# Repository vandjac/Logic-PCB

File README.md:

## Table of Contents
***
1. [General Info](#general-info)
2. [Design Requirements](#design-requirements) 
   - [Boolean Logic](#boolean-logic)
   - [Flip Flops](#flip-flops)
   - [Power](#power)
   - [Silk Screen](#silk-screen)
   - [Dimensions](#dimensions)
3. [Detailed Schematic Info](#detailed-schematic-info)
   - [Input Power](#input-power)
      - [USB-C Connector](#usb-c-connector)
      - [5V to 3.3V Linear Regulator](#linear-regulator)
      - [On/Off Switch](#power-switch)
      - [Battery Considerations](#battery-considerations)
   - [Buttons](#buttons)
   - [LEDs](#leds)
   - [Logic Gates](#logic-gates)
      - [NOT Gate](#not-gate)
      - [AND Gate](#and-gate)
      - [OR Gate](#or-gate)
      - [NAND Gate](#nand-gate)
      - [NOR Gate](#nor-gate)
      - [XOR Gate](#xor-gate)
      - [XNOR Gate](#xnor-gate)
   - [Flip Flops and Latches](#flip-flops-and-latches)
      - [D Flip Flop](#d-flip-flop)
      - [JK Flip Flop](#jk-flip-flop)
      - [T Flip Flop](#t-flip-flop)
      - [SR Latch](#sr-latch)
   - [Adjustable Clock Generator](#adjustable-clock-generator)
   - [State Machine](#state-machine)
   - [Synchronous 3-Bit 0-5 Counter](#synchronous-3-bit-0-5-counter)
   - [Multiplexers and 16-Segment Display](#multiplexers-and-16-segment-display)
4. [KiCAD](#kicad)
   - [Schematic Design](#schematic-design)
   - [PCB Layout](#pcb-layout)
      - [Images](#images)
5. [Possible Improvements](#possible-improvements)
6. [Acknowledgements](#acknowledgements)

## General Info
***
This is a quick-turn promotional PCB made as an intern project for Gentex Corporation. It showcases digital logic concepts in an interactive format, and will be a useful reference for students studying digital electronics.

## Design Requirements
***
#### Boolean Logic
* The design shall include the following Boolean logic gates:
   - AND 
    - OR 
    - XOR 
    - NOR 
    - NAND 
    - NOT 
    - XNOR 
* The design shall electrically demonstrate each logic gate. 
* The design shall include a silk screen that captures all of the logic gate truth tables. 
* The design shall include 2 inputs for each logic gate. 
#### Flip Flops
* The design shall implement a minimum of one (1) flip-flop. 
* The design shall electrically demonstrate all implemented flip-flops. 
* The design shall include a silk screen that captures each implemented flip-flop truth table. 
#### Power
* The design shall operate on 3.0V power. 
* The design shall be powered from either a coin cell battery, or external power supply. 
#### Silk Screen
* The design shall implement the Gentex logo on the silk screen layer. 
* The design shall implement the designer's college on the silk screen layer. 
#### Dimensions
* The design shall be implemented on a 3”x5” PCB. 
## [Detailed Schematic Info](https://github.com/vandjac/Logic-PCB/files/12321933/Logic-PCB-Schematic.pdf)
***
### Input Power
***
According to the project requirements, the board had to operate at 3V. When choosing input power, that left us with a couple options. Either we could use power from a USB input, or we could use a coin cell battery. Each had their advantages, but we decided on using USB power only. Although the coin cell battery allows for the board to be portable, it didn’t have enough capacity or current sourcing capabilities to be worth the addition.

We did a power analysis on our design to determine the max current that would theoretically be drawn. With 17 LEDs pulling 5-10mA, a max of 8 segments of the 16-digit display being on at 10mA, and the linear regulator at 45mA, our max current draw was around 200-300mA.

#### USB-C Connector

This USB-C connector is power only, which means it has fewer pins than a standard USB-C jack. This makes the pads bigger and easier to solder onto. The pins that are included are 2 VBUS, 2 GND, and 2 CC pins. The CC pins are used to regulate the current draw from the power source. In order to activate the power source, we have to add a 5.1k resistor to each CC pin. The USB-C should be able to supply 5V at up to 500mA, which should be enough for all functions on the board.

#### Linear Regulator

The chosen linear regulator can convert 5V to 3.3V with a max output current of 400mA. Another consideration for the regulator is heat dissipation, which could be problematic at max output current. The calculation for determining the temperature of the part is as follows:

Rthja×voltage drop×current draw

With the SOT-223 package, the temperature comes out to (87)(1.7)(0.4)=59.16°C

With the DPAK package, the temperature comes out to (72.5)(1.7)(0.4)=49.3°C

The industry standard is that anything over 60°C is too hot to touch, so the DPAK package is more appropriate for this case. This package is larger than the SOT-223.

The circuit design was copied from the datasheet for the linear regulator. The datasheet provides different configurations depending on the desired output voltage. A .1u bypass capacitor is also added to the output to smooth out voltage spikes.

#### Power Switch

The main consideration for the switch was how much current it could handle, since the entire power for the board was being routed through the switch. For the JS203011JAQN switch being used, the datasheet gives a contact rating of 0.3A@6VDC. Since we’re using 3V power, we should be able to get more than 0.3A through it, if needed.

#### Battery Considerations

In the event that someone would want to add a battery to the board, we have kept the schematics for the battery in the design, but commented out. If a battery were to be added in conjunction with USB power, it would be necessary to ensure that the two power sources don’t fight. To do so, Schottky diodes are placed on the 3V outputs of the battery holder and the linear regulator. These diodes have a low voltage drop (0.3V) and block current from flowing back into the battery or regulator. 

In reality, the Schottky diode on the regulator wouldn’t be doing much. This is because the regulator outputs a constant 3.3V, while the battery will always be at 3V or less. Therefore, current would only try to flow from the regulator to the battery. However, it is good practice to have Schottky diodes placed on both sources.

### Buttons
***

Originally, we were planning on having individual buttons for each logic gate and flip flop. We quickly realized that would be a waste of space. Now, we have two buttons (labeled A and B) that control all the logic gates and flip flops on the board. 

Each button has a pulldown resistor and two capacitors. The pulldown is there to make sure the button line is held low when the button is not pressed. The 1u capacitor helps to debounce the button, and the .1u capacitor is a bypass capacitor to eliminate voltage spikes. 

As for the specific button chosen, we simply found one in a small 6x6mm package that Gentex had in stock.

### LEDs
***
Each LED is set up to run at a max of 10mA. The LEDs have a voltage drop of 2V. 3.3V is taken from the pins on the ICs or from VCC, depending on the circuit. Therefore, we are left with V=IR, where V=1.3, I=13mA, and R=100Ω. That can easily be changed to V=1.3, I=6.5mA, and R=200Ω with a change of resistors.

Because we have the LEDs sinking current from ICs, we had to ensure that each IC was capable of sinking 10mA of current. The ICs we chose have that capability.

### Logic Gates
***
Logic gates are fundamental building blocks of digital circuits and are used to perform logical operations. According to the project requirements, the common 7 logic gates: AND, OR, NOT, XOR, NOR, XNOR, NAND. This was implemented with the use of NPN, PNP, P-channel, N-channel CMOS transistors, LEDs, resistors, and buttons A & B.

#### NOT Gate

The NOT gate, also known as an inverter, is a logical component that takes a single input signal and generates an output signal that is the inverse of the input. Specifically, when the input signal is at a high state (1), the output signal is at a low state (0), and conversely, when the input is low (0), the output is high (1). To achieve this functionality, a circuit was designed in which the power flows through a resistor and an LED connected to the collector of a PNP transistor. Initially, when the board is powered on, the LED is lit, indicating a high (1) output as button A remains untouched, signifying a low (0) input. However, when button A is pressed, causing a high (1) input, power is directed through the base of the PNP transistor, resulting in the LED being turned off, thereby representing a low (0) output state.

Truth Table:

| Input | Output |
|:---------:|:---------:|
| 0 | 1 |
| 1 | 0 |

#### AND Gate

The AND gate is a logic circuit that takes two or more input signals and generates a single output signal. The output signal is set to low (0) whenever any of the input signals are low (0). However, if all the input signals are high (1), the output will be high (1) as well. 

To implement this logic, the AND gate circuit utilizes two NPN transistors connected in series in the collector-emitter configuration with a resistor and an LED connected to the emitter. Initially, when the circuit is powered on, the LED remains off, indicating a low (0) output because neither button A nor B has been pressed, and no power flows through the transistors to activate the LED. Since the transistors are in series, pressing only one button (making it high) while the other remains low (0) continues to prevent power from reaching the LED, keeping the output low (0). However, when both buttons are pressed (making them high), power flows through both transistors, causing the LED to turn on/high (1) and indicating a high output.

Truth Table:

| Input A | Input B | Output |
|:---------:|:---------:|:---------:|
| 0 | 0 | 0 |
| 0 | 1 | 0 |
| 1 | 0 | 0 |
| 1 | 1 | 1 |

#### OR Gate

The OR gate is a logic gate that takes two or more input signals and produces a single output signal. The output signal is set to high (1) when any of the input signals is high (1). However, if all input signals are low (0), the output will be low (0) as well.

To implement this logic, the OR gate circuit utilizes two NPN transistors connected in parallel, with their collectors and emitters linked together. Additionally, a resistor and an LED are connected to the emitters. When the circuit is powered on, the LED remains off, indicating a low (0) output state. This occurs because neither button A nor B has been pressed, and therefore no power is flowing through either transistor to activate the LED.

When only one of the input buttons is pressed, while the other remains unpressed, the power will still flow through the corresponding transistor to activate the LED, resulting in a high (1) output. This is due to the parallel configuration of the transistors, which allows the output to remain high (1) even when both buttons are pressed and both transistors are conducting.

Truth Table:

| Input A | Input B | Output |
|:---------:|:---------:|:---------:|
| 0 | 0 | 0 |
| 0 | 1 | 1 |
| 1 | 0 | 1 |
| 1 | 1 | 1 |

#### NAND Gate

The NAND gate is a logical combination of an AND gate followed by a NOT gate (inverter). It accepts two or more input signals and produces an inverted output, which remains high (1) unless all the inputs are high (1).

To implement this logic, the NAND gate circuit utilizes two P-channel CMOS transistors connected in parallel, with their collectors and emitters linked together. Additionally, a resistor and an LED are connected to the emitters. There are also two N-channel CMOS transistors connected in series, with their collectors connected to the resistor and LED. Buttons A and B are respectively connected to the base of one P-channel and one N-channel transistor.

When the circuit is powered on, the LED will be initially on, representing a high (1) output. This occurs because neither button A nor B has been pressed, causing power to flow through both P-channel transistors and activating the LED. If only one of the input buttons is pressed, while the other remains unpressed, the power will still reach the LED, activating it, and resulting in a high (1) output. This is due to the parallel configuration of the P-channel transistors.

However, when both buttons are pressed, causing both P-channel transistors to turn off (low), the LED will be turned off (low) as well. This is because of the parallel configuration of the transistors, causing the output to turn off (low) in this scenario. The opposite behavior would occur for the N-channel transistors, but since the P-channel transistors are off (low), the LED remains off (low).

Truth Table:

| Input A | Input B | Output |
|:---------:|:---------:|:---------:|
| 0 | 0 | 1 |
| 0 | 1 | 1 |
| 1 | 0 | 1 |
| 1 | 1 | 0 |

#### NOR Gate

The NOR gate is a logical combination of an OR gate followed by a NOT gate (inverter). It accepts two or more input signals and produces an inverted output, which remains low (0) only when all inputs are high (1).

To implement this logic, the NOR gate circuit utilizes two P-channel CMOS transistors connected in series, in the collector-emitter configuration. Additionally, a resistor and an LED are connected to the emitter. There are also two N-channel CMOS transistors connected in parallel, with their collectors linked to the resistor and LED. Buttons A and B are respectively connected to the base of one P-channel and one N-channel transistor.

When the circuit is powered on, the LED will be initially on, representing a high (1) output. This happens because neither button A nor B has been pressed, allowing power to flow through both P-channel transistors, activating the LED. However, if only one of the input buttons is pressed, while the other remains unpressed, the power will not reach the LED, preventing it from activating. As a result, the output will be off/low (0). This behavior is due to the series configuration of the P-channel transistors.

Likewise, when both buttons are pressed, causing both N-channel transistors to turn off/low (0), the LED will be turned off/low (0) as well. This occurs because of the parallel configuration of the transistors, resulting in the output remaining off/low (0) in this situation. The opposite behavior would occur for the N-channel transistors, but since the P-channel transistor is off/low (0), the LED remains off/low (0).

Truth Table:

| Input A | Input B | Output |
|:---------:|:---------:|:---------:|
| 0 | 0 | 1 |
| 0 | 1 | 0 |
| 1 | 0 | 0 |
| 1 | 1 | 0 |

#### XOR Gate

The XOR gate, a fundamental logical combination of basic gates, operates on two input signals and generates a singular output signal with a high (1) state when the inputs are dissimilar (one is high while the other is low). Conversely, if both inputs are identical (both high or both low), the output assumes a low (0) state. The implementation of this gate involved the utilization of a chip sourced from Diodes Inc.. The selection of this particular component was based on its ability to meet the criteria for current and voltage requirements, as well as its compact size and cost-effectiveness.

Truth Table:

| Input A | Input B | Output |
|:---------:|:---------:|:---------:|
| 0 | 0 | 0 |
| 0 | 1 | 1 |
| 1 | 0 | 1 |
| 1 | 1 | 0 |

#### XNOR Gate

The XNOR gate, a logical combination of an XOR gate followed by a NOT gate (inverter), serves to process two input signals and yield an output signal that assumes a high state (1) exclusively when the inputs are identical (both high or both low). Conversely, if the inputs are dissimilar, the output assumes a low state (0). The practical realization of this functionality involved the adoption of a chip sourced from the company Nexperia. This was selected for its ability to fulfill the necessary criteria concerning current and voltage requirements, as well as the chip’s ability to meet the criteria for current and voltage requirements, as well as its compact size and cost-effectiveness.

Truth Table:

| Input A | Input B | Output |
|:---------:|:---------:|:---------:|
| 0 | 0 | 1 |
| 0 | 1 | 0 |
| 1 | 0 | 0 |
| 1 | 1 | 1 |

### Flip Flops and Latches
***
Latches and flip-flops are fundamental building blocks in digital logic circuits used to store and synchronize data.

A latch is a simple digital storage element that can hold one bit of data. It is based on a bistable circuit, which means it has two stable states. Latches are level-sensitive and can be sensitive to glitches and timing issues. They are mainly used in asynchronous circuits and for temporary storage.

A flip-flop is a more advanced digital storage element that can also hold one bit of data. It is also based on a bistable circuit but operates with a clock signal, making it edge-triggered. Since flip-flops are edge-triggered they are more robust against glitches and can be easily synchronized in sequential circuits, making them the preferred choice for most synchronous digital systems.

There is a .1u bypass capacitor on each VCC pin to eliminate voltage spikes for each flip flop. 

#### D Flip Flop

The D flip-flop has a data input (D), a clock input (usually called CLK or CP), and an output (Q). On the rising (or falling) edge of the clock signal, the D flip-flop stores the value present at the data input. The stored value is then available at the output (Q). D flip-flops are widely used for sequential circuits and in synchronous systems.

The D flip flop circuit has one button input (D) and a CLK input. It has inverted set and reset pins that are both tied to VCC to prevent them from activating. Both Q and !Q drive LEDs.

Truth Table:

| D | Q | Qt |
|:---------:|:---------:|:---------:|
| 0 | 0 | 0 |
| 0 | 1 | 1 |
| 1 | 0 | 0 |
| 1 | 1 | 1 |

#### JK Flip Flop

The JK flip-flop has two data inputs: J and K, along with a clock input and an output. The behavior of the JK flip-flop is similar to the D flip-flop, but it has the additional feature of allowing the toggling of the output (Q) when both J and K inputs are active simultaneously.

The JK flip flop circuit has two button inputs (1J and 1K) and a CLK input. The IC being used is a dual JK flip flop, but only one of them is being used, so half of the pins aren’t being used. An inverted reset pin is tied to VCC to prevent it from activating. Both Q and !Q drive LEDs.

It is also a negative edge triggered flip flop, meaning it becomes active when the clock signal goes from high to low, and ignores the low- to-high transition. This means it will be activated on the button release instead of the press.

Truth Table:

| J| K | Qt | Q(t+1) |
|:---------:|:---------:|:---------:|:---------:|
| 0 | 0 | 0 | 0 |
| 0 | 0 | 1 | 1 |
| 0 | 1 | 0 | 0 |
| 0 | 1 | 1 | 0 |
| 1 | 0 | 0 | 1 |
| 1 | 0 | 1 | 1 |
| 1 | 1 | 0 | 1 |
| 1 | 1 | 1 | 0 |

#### T Flip Flop
D

The T flip-flop has a single input (T) and a clock input (usually called CLK or CP), along with an output (Q). On each rising (or falling) edge of the clock signal, the T flip-flop toggles its output (Q) based on the value at the T input.

The implementation of the T flip flop uses the same chip as the JK flip flop. A T flip flop can be built from a JK flip flop by tying together the two inputs. The T flip flop is also on a different part of the board, because it is used in the counter (which is discussed more below). Since it is being used in the counter it also doesn’t use button inputs. To display the input, an LED is placed on the combined J&K input. Although it’s not displayed in this screenshot, both Q and !Q also drive LEDs.

Truth Table:

| T | Q | Qt |
|:---------:|:---------:|:---------:|
| 0 | 0 | 0 |
| 0 | 1 | 1 |
| 1 | 0 | 1 |
| 1 | 1 | 0 |

#### SR Latch

The SR latch has two inputs: Set (S) and Reset (R). When the Set input is asserted (usually logic high), the latch stores the value '1'. Conversely, when the Reset input is asserted (usually logic high), the latch stores the value '0'. If both inputs are active simultaneously, the behavior is unpredictable, and this condition should be avoided.

This is the only latch shown on the board. It is also implemented differently from the flip flops. Since latches are simpler, the SR could be built using two NOR gates instead of a single IC. This allows the structure and function of an SR latch to be better understood. In the SR latch configuration, each NOR gate has a button input. Each NOR gate output is tied to the second input of the other NOR gate. The outputs also drive LEDs.

Truth Table:

| S | R | Qt | Q(t+1) |
|:---------:|:---------:|:---------:|:---------:|
| 0 | 0 | 0 | 0 |
| 0 | 0 | 1 | 1 |
| 0 | 1 | 0 | 0 |
| 0 | 1 | 1 | 0 |
| 1 | 0 | 0 | 1 |
| 1 | 0 | 1 | 1 |
| 1 | 1 | 0 | X |
| 1 | 1 | 1 | X |

### Adjustable Clock Generator
***

It was necessary to add a timer to produce a clock signal that’s used by the flip flops. The timer circuit is mostly taken from its datasheet (the circuit for A-stable operation). The component values were derived from equations found on the datasheet. We chose RA to be 1kΩ and C to be 1u. That leaves RB as the value to change to affect the frequency of the clock. 

Period = 0.693(RA+2RB)C

Frequency = 1.44/((RA+2RB)C)

Using these equations we can find a potentiometer that can vary the frequency in a usable range. We settled on a 10Ω to 2MΩ potentiometer, which allows for a frequency sweep of .001s to 1.387s. 

The potentiometer was placed in series with another resistor (R32, 1kΩ) so it doesn’t effectively short when the potentiometer is at its lowest resistance.

Two extra capacitors were added as well. A 0.1uF is used for decoupling on power input to the chip. Another decoupling cap is placed from CONT to GND improves operation by reducing noise on the rising edge of the clock signal. This info is also found in the datasheet.

Finally, an LED is placed on the clock output so the frequency can be visualized.

### State Machine
***
The state machine is the most complex circuit on this board. It is intended to display the use of flip flops to switch between different states. The state machine being implemented here is a Moore state machine, which means its next state is only determined by its current state.

#### Synchronous 3-Bit 0-5 Counter

To build a counter, first you need to create a state transition table. This table includes the current state, the corresponding next state, and whether that bit needs to toggle or not. 

This table is then used to create Karnaugh maps for each toggle bit. The Karnaugh maps are filled in with values from the toggle bit portion of the state transition table, in relation to the current state.

From the Karnaugh maps we got simplified expressions for each toggle bit, which will be used for each T flip flop. The T flip flops are implemented with the logic from the expressions. For example, if T1=!AC, then T flip flop 1 will accept an input from the inverse of the output of T flip flop 0 ANDed with the output of T flip flop 2. 

The chips being used all have decoupling capacitors, and the input and output of each T flip flop are visualized using LEDs.

#### Multiplexers and 16 Segment Display

The output of the counter will need to be translated into letters in the word “GENTEX”. To do so, we used multiplexers. These muxes take the counter as their select bits, and then each of the inputs are tied to either 3V or GND, depending on whether a segment needs to be turned on or not.

Although there are 16 segments in the display, only 9 muxes are needed. This is because some of the segments always turn on and off at the same times in the letters of GENTEX, so a single mux can drive both segments.

In order to determine which mux inputs to tie high and low, we created a table. The table includes the counter input (with bits a, b, and c) and a column for each segment in the display. The table is then filled in with a 1 if the segment is on at that counter value, and 0 if it is not. Identical columns are colored as such. For example, segments A and B have a sequence of 110110. Therefore, the mux that drives A and B should have inputs 1, 2, 4, and 5 tied to 3V. Inputs 3 and 6 should be tied to GND. 

The outputs of each mux are capable of sourcing at least 10mA of current. A current limiting resistor is placed between each output and LED segment.

## KiCAD
***
#### [Schematic Design](https://github.com/vandjac/Logic-PCB/files/12321933/Logic-PCB-Schematic.pdf)

When designing the schematics to the circuits on the PCB, an important step was to find the components needed as well as assigning the footprints and values to them. This involved researching for parts and then finding the selected part online and importing it to KiCAD. This process was streamlined by using a tool called Samacsys KiCAD Libraries. Using this tool, it was possible to search the part needed, see if it had a footprint, datasheet, etc., and import it to the KiCAD library all with a couple clicks. There was only one footprint that was not found, the power USB-C, and so a handmade footprint was made using KiCAD based on the datasheet of the component. Boxes were also drawn around circuits that were in some way related as to clarify sections of the board because the point of the board is to explain how things work.

To tie the schematic to the QR code, and because this project is meant to be used as a teaching tool, a QR code was placed on the layout that links to the GitHub Repository. This not only provides an explanation for steps taken in the process of the making of the PCB, but also provides the schematic and other useful images and explanations.

#### [PCB Layout](#images)
0.15mm traces were used throughout the board. This was the chosen diameter because there is not a lot of current flowing through the board so wide traces are not as necessary. This also ensured that all the connections could be made as the 8-1 MUXs were small QFNs which would not be possible if the traces were much larger. All of the components were designed to be on the “top” side of the board to ensure it would lay flat, the only through hole component is the 16-seg display. As few vias as possible were used, however there were a lot around the MUXs due to the nature of the chosen chips.

Silkscreen was used heavily in the layout of the PCB. Artificial silkscreen “traces” were drawn from the buttons A & B as well as the clock to the outlines of their respective recipient symbols. These symbols were made by converting an image to a footprint, and then putting the footprint as the silkscreen layer. The same was done for the front and back of the board using the built-in KiCAD image converter tool. The logos were done in a similar fashion, except that they were converted to the mask layer instead of the silkscreen layer.

#### Images
***
#### KiCAD 3D view (Front)

#### KiCAD 3D view (Back)

#### KiCAD Layout (Front)

#### KiCAD Layout (Back)

#### KiCAD Routing (Front)

#### KiCAD Routing (Back)

## Possible Improvements
***
- The switch currently being used is a right-angle switch, pointed in a direction on the board that makes it somewhat difficult to access. The switch should either be moved to the side of the board, or a vertical switch should be used.
- As discussed in the “Battery Considerations” section, a battery could be added to improve portability of the board.
- If a battery is added, thought could be put into whether making it rechargeable through USB-C or a solar panel would be worthwhile.
- It would entail a complete redesign of the board, but implementing everything on a small microcontroller could allow you to reduce the dimensions of the board or add many more features to the board in the same dimensions.

## Acknowledgements
***
Thanks to Tom Case and Nicholas Young for defining this project and doing a thorough design review with us.

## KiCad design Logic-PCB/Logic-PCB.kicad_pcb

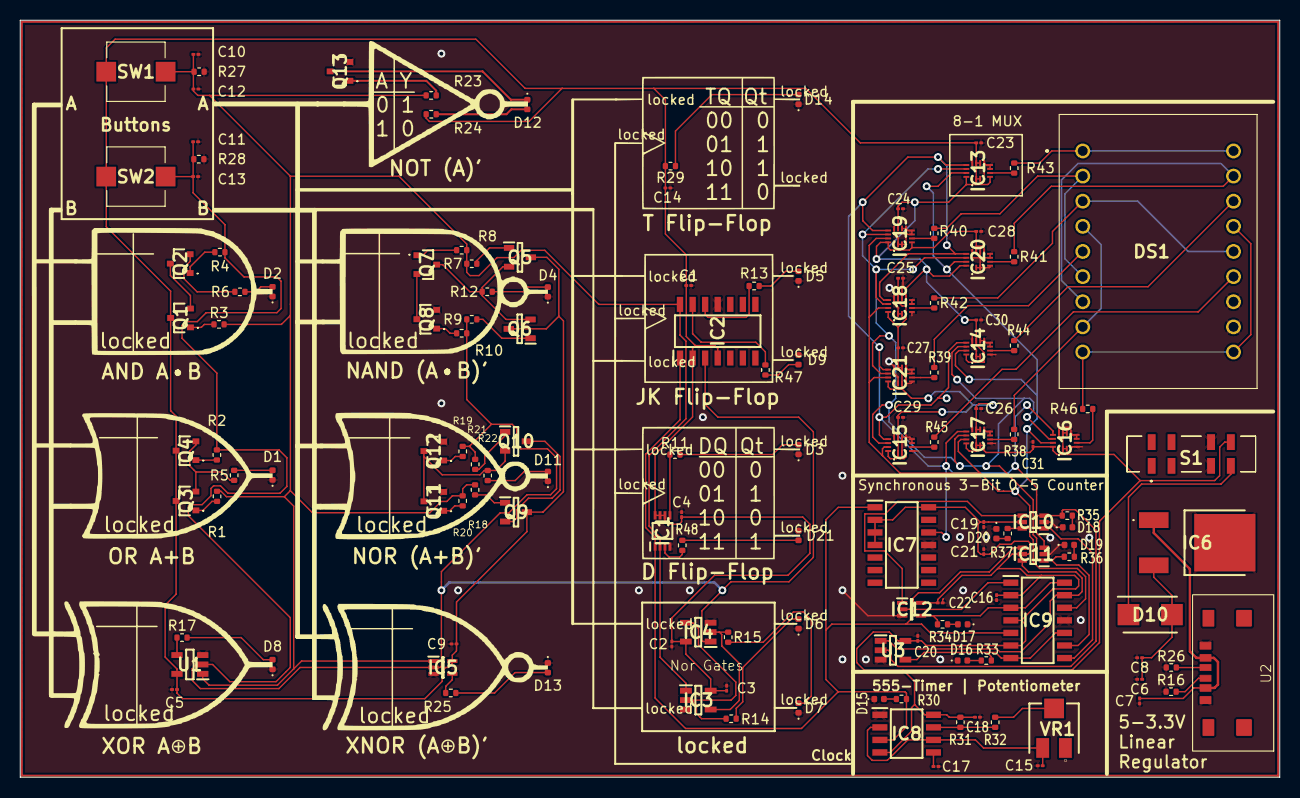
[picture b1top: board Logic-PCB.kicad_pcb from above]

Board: 2 copper layers, 127.3 x 76.5 mm, 152 parts (0 on the bottom side), 90 nets.

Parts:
AND A•B: LOGO; AND
C1, C2, C3, C4, C5, C8, C9, C12, C13, C14, C16, C18, C19, C20, C21, C22, C23, C24, C25, C26, C27, C28, C29, C30, C31: .1u; C_01005_0402Metric
C6: 10u; C_01005_0402Metric
C7: 100n; C_01005_0402Metric
C10, C11, C15: 1u; C_01005_0402Metric
C17: .01u; C_01005_0402Metric
D1, D2, D3, D4, D5, D6, D7, D8, D9, D11, D12, D13, D14, D15, D16, D17, D18, D19, D20, D21: LED; LED_0402_1005Metric
D10: LSM115JE3_TR13; DIOM5436X330N
D Flip-Flop: LOGO; Flip-Flop
DS1: PSA08-11GWA; PSA0811GWA
IC1: 74LVC1G74DC-Q100H; SOP50P310X100-8N
IC2, IC7, IC9: 74HC73D,653; SOIC127P600X175-14N
IC3, IC4: SN74LVC1G02DBVR; SOT95P280X145-5N
IC5: 74AUP1T87GWH; SOT65P212X110-5N
IC6: NCV4274CDT33RKG
IC8: TLC555QDRQ1; SOIC127P600X175-8N
IC10, IC11: SN74LVC1G11MDCKREP; SOP65P210X110-6N
IC12: 74AUP1G32GW-Q100H; SOT65P212X110-5N
IC13, IC14, IC15, IC16, IC17, IC18, IC19, IC20, IC21: TMUX1208QRSVRQ1
JK Flip-Flop: LOGO; JK-Latch
NAND (A•B)': LOGO; NAND
NOR (A+B)': LOGO; NOR
NOT (A)': LOGO; NOT
OR A+B: LOGO; OR
Q1, Q2, Q3, Q4: BC847,215; BC847215
Q5, Q6, Q9, Q10: PMV100EPAR; SOT95P230X110-3N
Q7, Q8, Q11, Q12: 2N7002_HAMR; 2N7002HAMR
Q13: BC858B,235; BC858B235
R1, R2, R3, R4, R7, R8, R9, R10, R18, R19, R20, R21, R23: 5.6k; R_0402_1005Metric
R5, R6, R11, R12, R13, R14, R15, R17, R22, R24, R25, R29, R30, R33, R34, R35, R36, R37, R38, R39, R40, R41, R42, R43, R44, R45, R46, R47, R48: 100; R_0402_1005Metric
R16, R26: 5.1k; R_0402_1005Metric
R27, R28: 10k; R_0402_1005Metric
R31, R32: 1k; R_0402_1005Metric
S1: JS203011JAQN
SW1, SW2: SW_Push; SKPMBHE010
T Flip-Flop: LOGO; Flip-Flop
U1: 74AHC1G86W5-7; SOT95P285X130-5N
U2: USB-C UJC-HP-G-5-SMT-TR
U3: NC7S08M5X; SOT95P280X145-5N
VR1: 3314J-2-105E; 3314J-1
XNOR (A⊕B)': LOGO; XNOR
XOR A⊕B: LOGO; XOR

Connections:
3V before switch: D10.1, S1.4 (NO_1)
+3V0: C1.1, C2.1, C3.1, C4.1, C5.1, C9.1, C14.1, C16.1, C18.1, C19.1, C20.1, C21.1, C22.1, C23.1, C24.1, C25.1, C26.1, C27.1, C28.1, C29.1, C30.1, C31.1, IC1.6 (~RD), IC1.7 (~SD), IC1.8 (VCC), IC2.2 (1~R), IC2.4 (VCC), IC3.5 (VCC), IC4.5 (VCC), IC5.5 (VCC), IC7.2 (1~R), IC7.3 (1K), IC7.4 (VCC), IC7.14 (1J), IC8.4 (RESET), IC8.8 (VDD), IC9.2 (1~R), IC9.4 (VCC), IC9.6 (2~R), IC10.5 (VCC), IC11.5 (VCC), IC12.5 (VCC), IC13.2 (S1), IC13.3 (S2), IC13.5 (S4), IC13.10 (S5), IC13.11 (VDD), IC13.16 (EN), IC14.4 (S3), IC14.11 (VDD), IC14.16 (EN), IC15.2 (S1), IC15.4 (S3), IC15.11 (VDD), IC15.16 (EN), IC16.2 (S1), IC16.3 (S2), IC16.10 (S5), IC16.11 (VDD), IC16.16 (EN), IC17.2 (S1), IC17.3 (S2), IC17.4 (S3), IC17.10 (S5), IC17.11 (VDD), IC17.16 (EN), IC18.4 (S3), IC18.9 (S6), IC18.11 (VDD), IC18.16 (EN), IC19.5 (S4), IC19.11 (VDD), IC19.16 (EN), IC20.9 (S6), IC20.11 (VDD), IC20.16 (EN), IC21.3 (S2), IC21.10 (S5), IC21.11 (VDD), IC21.16 (EN), Q1.3, Q3.3, Q4.3, Q5.3, Q6.3, Q9.3, R24.1, R29.2, R31.2, S1.8 (NO_2), SW1.1, SW2.1, U1.5 (VCC), U3.5 (VCC)
+5V: C7.2, IC6.1 (INPUT), U2.2 (Vbus1), U2.5 (Vbus2)
Button A: C10.1, C12.1, IC1.2 (D), IC2.14 (1J), IC3.1 (A), IC5.1 (B), R1.1, R3.1, R7.1, R8.1, R18.2, R20.1, R23.1, R27.2, SW1.2, U1.1 (A)
Button B: C11.1, C13.1, IC2.3 (1K), IC4.1 (A), IC5.2 (A), R2.1, R4.1, R9.1, R10.1, R19.1, R21.1, R28.2, SW2.2, U1.2 (B)
CLK: IC1.1 (CP), IC2.1 (1~CP), IC7.1 (1~CP), IC8.3 (OUT), IC9.1 (1~CP), IC9.5 (2~CP), R30.1
GND: C1.2, C2.2, C3.2, C4.2, C5.2, C6.2, C7.1, C8.2, C9.2, C10.2, C11.2, C12.2, C13.2, C14.2, C15.2, C16.2, C17.2, C18.2, C19.2, C20.2, C21.2, C22.2, C23.2, C24.2, C25.2, C26.2, C27.2, C28.2, C29.2, C30.2, C31.2, D1.1 (K), D2.1 (K), D3.1 (K), D4.1 (K), D5.1 (K), D6.1 (K), D7.1 (K), D8.1 (K), D9.1 (K), D11.1 (K), D13.1 (K), D14.1 (K), D15.1 (K), D16.1 (K), D17.1 (K), D18.1 (K), D19.1 (K), D20.1 (K), D21.1 (K), DS1.11 (COM_A), DS1.12 (K_DP), IC1.4 (GND), IC2.11 (GND), IC3.3 (GND), IC4.3 (GND), IC5.3 (GND), IC6.2 (GROUND), IC7.11 (GND), IC8.1 (GND), IC9.11 (GND), IC10.2 (GND), IC11.2 (GND), IC12.3 (GND), IC13.4 (S3), IC13.7 (S8), IC13.8 (S7), IC13.9 (S6), IC13.12 (GND), IC14.2 (S1), IC14.3 (S2), IC14.5 (S4), IC14.7 (S8), IC14.8 (S7), IC14.9 (S6), IC14.10 (S5), IC14.12 (GND), IC15.3 (S2), IC15.5 (S4), IC15.7 (S8), IC15.8 (S7), IC15.9 (S6), IC15.10 (S5), IC15.12 (GND), IC16.4 (S3), IC16.5 (S4), IC16.7 (S8), IC16.8 (S7), IC16.9 (S6), IC16.12 (GND), IC17.5 (S4), IC17.7 (S8), IC17.8 (S7), IC17.9 (S6), IC17.12 (GND), IC18.2 (S1), IC18.3 (S2), IC18.5 (S4), IC18.7 (S8), IC18.8 (S7), IC18.10 (S5), IC18.12 (GND), IC19.2 (S1), IC19.3 (S2), IC19.4 (S3), IC19.7 (S8), IC19.8 (S7), IC19.9 (S6), IC19.10 (S5), IC19.12 (GND), IC20.2 (S1), IC20.3 (S2), IC20.4 (S3), IC20.5 (S4), IC20.7 (S8), IC20.8 (S7), IC20.10 (S5), IC20.12 (GND), IC21.2 (S1), IC21.4 (S3), IC21.5 (S4), IC21.7 (S8), IC21.8 (S7), IC21.9 (S6), IC21.12 (GND), Q8.2, Q11.2, Q12.2, Q13.2, R16.1, R26.1, R27.1, R28.1, S1.3 (COM_1), S1.7 (COM_2), U1.3 (GND), U2.1 (GND1), U2.6 (GND2), U3.3 (GND)
unnamed: D1.2 (A), R5.1
unnamed: D2.2 (A), R6.1
unnamed: D3.2 (A), R11.2
unnamed: D4.2 (A), R12.1
unnamed: D5.2 (A), R13.1
unnamed: D6.2 (A), R14.1
unnamed: D7.2 (A), R15.1
unnamed: D8.2 (A), R17.2
unnamed: D9.2 (A), R47.1
unnamed: D11.2 (A), R22.1
unnamed: D12.2 (A), R24.2
unnamed: D12.1 (K), Q13.3
unnamed: D13.2 (A), R25.2
unnamed: D14.2 (A), R29.1
unnamed: D15.2 (A), R30.2
unnamed: D16.2 (A), R33.1
unnamed: D17.2 (A), R34.1
unnamed: D18.2 (A), R35.1
unnamed: D19.2 (A), R36.1
unnamed: D20.2 (A), R37.1
unnamed: D21.2 (A), R48.1
unnamed: DS1.1 (K_A), DS1.18 (K_B), R43.2
unnamed: DS1.16 (K_C), R44.2
unnamed: DS1.13 (K_D), R45.2
unnamed: DS1.9 (K_F), DS1.10 (K_E), DS1.15 (K_P), R46.2
unnamed: DS1.4 (K_H), DS1.8 (K_G), R38.2
unnamed: DS1.3 (K_K), DS1.14 (K_R), R42.2
unnamed: DS1.2 (K_M), DS1.6 (K_S), R40.2
unnamed: DS1.7 (K_T), DS1.17 (K_N), R41.2
unnamed: DS1.5 (K_U), R39.2
unnamed: IC1.5 (Q), R11.1
unnamed: IC1.3 (~Q), R48.2
unnamed: IC2.12 (1Q), R13.2
unnamed: IC2.13 (1~Q), R47.2
unnamed: IC3.2 (B), IC4.4 (Y), R14.2
unnamed: IC3.4 (Y), IC4.2 (B), R15.2
unnamed: IC5.4 (Y), R25.1
unnamed: C6.1, C8.1, D10.2, IC6.3 (OUTPUT)
unnamed: C17.1, IC8.5 (CONT)
unnamed: IC8.7 (DISCH), R31.1, R32.1
unnamed: C15.1, IC8.2 (TRIG), IC8.6 (THRES), VR1.3 (CW)
unnamed: IC9.7 (2J), IC9.10 (2K), R33.2, U3.4 (Y)
unnamed: IC9.8 (2~Q), IC10.1 (A)
unnamed: IC7.12 (1Q), IC10.3 (B), IC11.3 (B), IC13.13 (A2), IC14.13 (A2), IC15.13 (A2), IC16.13 (A2), IC17.13 (A2), IC18.13 (A2), IC19.13 (A2), IC20.13 (A2), IC21.13 (A2), R35.2, U3.2 (B)
unnamed: IC9.12 (1Q), IC10.6 (C), IC13.15 (A0), IC14.15 (A0), IC15.15 (A0), IC16.15 (A0), IC17.15 (A0), IC18.15 (A0), IC19.15 (A0), IC20.15 (A0), IC21.15 (A0), R37.2
unnamed: IC10.4 (Y), IC12.1 (B)
unnamed: IC9.9 (2Q), IC11.1 (A), IC13.14 (A1), IC14.14 (A1), IC15.14 (A1), IC16.14 (A1), IC17.14 (A1), IC18.14 (A1), IC19.14 (A1), IC20.14 (A1), IC21.14 (A1), R36.2
unnamed: IC9.13 (1~Q), IC11.6 (C), U3.1 (A)
unnamed: IC11.4 (Y), IC12.2 (A)
unnamed: IC9.3 (1K), IC9.14 (1J), IC12.4 (Y), R34.2
unnamed: IC13.6 (D), R43.1
unnamed: IC14.6 (D), R44.1
unnamed: IC15.6 (D), R45.1
unnamed: IC16.6 (D), R46.1
unnamed: IC17.6 (D), R38.1
unnamed: IC18.6 (D), R42.1
unnamed: IC19.6 (D), R40.1
unnamed: IC20.6 (D), R41.1
unnamed: IC21.6 (D), R39.1
unnamed: Q1.1, R3.2
unnamed: Q1.2, Q2.3
unnamed: Q2.1, R4.2
unnamed: Q2.2, R6.2
unnamed: Q3.1, R1.2
unnamed: Q3.2, Q4.2, R5.2
unnamed: Q4.1, R2.2
unnamed: Q5.1, R7.2
unnamed: Q5.2, Q6.2, Q7.3, R12.2
unnamed: Q6.1, R9.2
unnamed: Q7.1, R8.2
unnamed: Q7.2, Q8.3
unnamed: Q8.1, R10.2
unnamed: Q9.1, R18.1
unnamed: Q10.1, R21.2
unnamed: Q10.2, Q11.3, Q12.3, R22.2
unnamed: Q9.2, Q10.3
unnamed: Q11.1, R20.2
unnamed: Q12.1, R19.2
unnamed: Q13.1, R23.2
unnamed: R17.1, U1.4 (Y)
unnamed: R16.2, U2.3 (CC1)
unnamed: R26.2, U2.4 (CC2)
unnamed: R32.2, VR1.2 (WIPER)

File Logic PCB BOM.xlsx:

Qty | Reference(s) | Value | Datasheet | Description | Manufacturer | Manufacturer Part Number | Digikey Link | Unit Price (At quantity of 10) | Gentex Part Number | In stock at Gentex?
26 | C1, C2, C3, C4, C5, C7, C8, C9, C12, C13, C14, C16, C18, C19, C20, C21, C22, C2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 | .1u | ~ | 0402 Capacitor |  | ~ | ~ | ~ | 176-0167-000 | Yes
1 | C6 | 10u | ~ | 0402 Capacitor |  | ~ | ~ | ~ | 176-0526-000 | Yes
3 | C10, C11, C15 | 1u | ~ | 0402 Capacitor |  | ~ | ~ | ~ | 176-0408-000 | Yes
1 | C17 | .01u | ~ | 0402 Capacitor |  | ~ | ~ | ~ | 176-0293-000 | Yes
16 | D2, D3, D4, D5, D6, D7, D8, D9, D10, D11, D12, D13, D15, D16, D17, D21 | LED | ~ | 0402 LED |  | ~ | ~ | ~ | 204-0359-000-GREEN 204-0360-000-BLUE 204-0361-000-ORANGE 204-0363-000-YELLOW 20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 | YesYesNONONOYes
1 | DS1 | PSA08-11GWA | https://componentsearchengine.com/Datasheets/1/PSA08-11GWA.pdf | LED Displays & Accessories AlphaNum Grn 568nm Common Anode | Kingbright | PSA08-11SURKWA | https://www.digikey.com/en/products/detail/kingbright/PSA08-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 | 3.85 | ~ | ~
1 | IC1 | 74LVC1G74DC-Q100H | https://assets.nexperia.com/documents/data-sheet/74LVC1G74_Q100.pdf | 74LVC1G74-Q100 - Single D-type flip-flop with set and reset; positive edge trig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 | Nexperia | 74LVC1G74DC-Q100H | https://www.digikey.com/en/products/detail/nexperia-usa-inc/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 | 0.57999999999999996 | 315-0669-000 | Yes
3 | IC2, IC7, IC9 | 74HC73D,653 | https://assets.nexperia.com/documents/data-sheet/74HC73.pdf | 74HC73 - Dual JK flip-flop with reset; negative-edge trigger@en-us | Nexperia | 74HC73D,653 | https://www.digikey.com/en/products/detail/nexperia-usa-inc/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 | 0.52400000000000002 | ~ | ~
2 | IC3, IC4 | SN74LVC1G02DBVR | http://www.ti.com/lit/gpn/sn74lvc1g02 | Single 2-Input Positive-NOR Gate | Texas Instruments | SN74LVC1G02DBVR | https://www.digikey.com/en/products/detail/texas-instruments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 | 0.28499999999999998 | ~ | ~
1 | IC5 | 74AUP1T87GWH | https://assets.nexperia.com/documents/data-sheet/74AUP1T87.pdf | 74AUP1T87 - Low-power 2-input EXCLUSIVE-NOR gate with voltage-leveltranslator@e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 | Nexperia | 74AUP1T87GWH | https://www.digikey.com/en/products/detail/nexperia-usa-inc/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 | 0.35699999999999998 | ~ | ~
1 | IC6 | NCV4274CDT33RKG | https://www.onsemi.com/pdf/datasheet/ncv4274c-d.pdf | ON SEMICONDUCTOR - NCV4274CDT33RKG - LDO, FIXED, 3.3V, 0.4A, -40 TO 150DEG C | onsemi | NCV4274CDT33RKG | No stock | 1.375 | 153-0166-000 | Yes
1 | IC8 | TLC555QDRQ1 | http://www.ti.com/lit/ds/symlink/tlc555-q1.pdf | TEXAS INSTRUMENTS - TLC555QDRQ1 - IC, TIMER, 8SOIC | Texas Instruments | TLC555QDRQ1 | https://www.digikey.com/en/products/detail/texas-instruments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 | 0.92700000000000005 | TLC555QDRQ1 | No
2 | IC10, IC11 | SN74LVC1G11MDCKREP | https://www.ti.com/lit/gpn/SN74LVC1G11-EP | Logic Gates EP Sgl 3-Input Pos AND Gate | Texas Instruments | SN74LVC1G11MDCKREP | https://www.digikey.com/en/products/detail/texas-instruments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 | 1.8740000000000001 | ~ | ~
2 | IC12, IC22 | 74AUP1G32GW-Q100H | https://assets.nexperia.com/documents/data-sheet/74AUP1G32_Q100.pdf | Low-power 2-input OR-gate@en-us | Nexperia | 74AUP1G32GW,125 | https://www.digikey.com/en/products/detail/nexperia-usa-inc/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 | 0.34599999999999997 | ~ | ~
9 | IC13, IC14, IC15, IC16, IC17, IC18, IC19, IC20, IC21 | TMUX1208QRSVRQ1 | https://www.ti.com/lit/gpn/tmux1208-q1?HQS=ti-null-null-sf-d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 | Multiplexer Switch ICs Automotive 5-V, 8:1, 1-channel multiplexer with 1.8-V lo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 | Texas Instruments | TMUX1208QRSVRQ1 | https://www.digikey.com/en/products/detail/texas-instruments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 | 1.222 | ~ | ~
2 | Q1, Q2 | BC847,215 | https://assets.nexperia.com/documents/data-sheet/BC847_SER.pdf | BC847 series - 45 V, 100 mA NPN general-purpose transistors | Nexperia | BC847,215 | https://www.digikey.com/en/products/detail/nexperia-usa-inc/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 | 0.13 | ~ | ~
4 | Q5, Q6, Q9, Q10 | PMV100EPAR | https://assets.nexperia.com/documents/data-sheet/PMV100EPA.pdf | NEXPERIA - PMV100EPAR - Power MOSFET, P Channel, 60 V, 2.2 A, 0.1 ohm, SOT-23, 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 | Nexperia | PMV100EPAR | https://www.digikey.com/en/products/detail/nexperia-usa-inc/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 | 0.41599999999999998 | ~ | ~
4 | Q7, Q8, Q11, Q12 | 2N7002_HAMR | https://assets.nexperia.com/documents/data-sheet/2N7002.pdf | 60 V, 300 mA N-channel Trench MOSFET VDS:60v ID:300 ma | Nexperia | 2N7002/HAMR | https://www.digikey.com/en/products/detail/nexperia-usa-inc/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 | 0.20799999999999999 | ~ | ~
1 | Q13 | BC858B,235 | https://assets.nexperia.com/documents/data-sheet/BC856_BC857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 | BC856; BC857; BC858 - PNP general purpose transistors | Nexperia | BC858B,235 | https://www.digikey.com/en/products/detail/nexperia-usa-inc/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 | 0.128 | ~ | ~
9 | R7, R8, R9, R10, R18, R19, R20, R21, R55 | 5.6k | ~ | 0402 Resistor |  | ~ | ~ | ~ | 116-0247-000 | Yes
29 | R5, R6, R11, R12, R13, R14, R15, R17, R22, R24, R25, R29, R30, R33, R34, R35, R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 | 100 | ~ | 0402 Resistor |  | ~ | ~ | ~ | 116-0130-000 | Yes
2 | R16, R26 | 5.1k | ~ | 0402 Resistor |  | ~ | ~ | ~ | 116-0204-000 | Yes
2 | R27, R28 | 10k | ~ | 0402 Resistor |  | ~ | ~ | ~ | 116-0013-000 | Yes
4 | R3, R4, R31, R32 | 1k | ~ | 0402 Resistor |  | ~ | ~ | ~ | 116-0007-000 | Yes
1 | R57 | 2K | ~ | 0402 Resistor |  | ~ | ~ | ~ | 116-0028-000 | Yes
2 | SW1, SW2 | SW_Push | https://tech.alpsalpine.com/e/products/detail/SKPMBHE010/ | SWITCH TACT SPST-NO .05A 16VDC | Alps Alpine | SKPMBHE010 | No stock | 0.68300000000000005 | 162-0015-000 | Yes
1 | U1 | 74AHC1G86W5-7 | https://componentsearchengine.com/Datasheets/2/74AHC1G86W5-7.pdf | DiodesZetex 74AHC1G86W5-7, XOR 2 Input XOR Schmitt Trigger, 2 5.5 V, 5-Pin SOT-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 | Diodes Inc. | 74AHC1G86W5-7 | https://www.digikey.com/en/products/detail/diodes-incorporat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 | 0.28100000000000003 | ~ | ~
1 | U2 | USB-C RECEPTACLE | https://www.cuidevices.com/product/resource/ujc-hp-g-5-smt-tr.pdf | USB-C | CUI Devices | UJC-HP-G-5-SMT-TR | https://www.digikey.com/en/products/detail/cui-devices/UJC-H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 | 0.64100000000000001 | ~ | ~
1 | U3 | NC7S08M5X | http://componentsearchengine.com/Datasheets/3/NC7S08M5X.pdf | Fairchild Semiconductor NC7S08M5X, 2-Input AND Logic Gate, 2 6 V, 5-Pin SOT-23 | onsemi | NC7S08M5X | No stock | ~ | 315-0500-000 | Yes
1 | VR1 | 3314J-1-205E | https://www.bourns.com/docs/Product-Datasheets/3314.pdf | TRIMMER 2M OHM 0.25W J LEAD TOP | Bourns | 3314J-1-205E | https://www.digikey.com/en/products/detail/bourns-inc/3314J-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 | 1.83 | ~ | ~

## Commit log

2023-06-20 Initial KiCad files
2023-07-06 stuff
2023-07-10 gates
2023-07-11 PCB 2
2023-07-11 remove pcb 2
2023-07-11 all the stuff
2023-07-11 Gates (R change)
2023-07-12 Decoupling Caps
2023-07-13 Removing pulldown resistors
2023-07-13 updates from meeting
2023-07-14 CMOS
2023-07-14 oops I didn't change the right schematic
2023-07-24 Routing and LEDs
2023-07-24 LEDs
2023-07-25 Layout
2023-07-25 Back info
2023-07-25 Back
2023-07-26 Update fp-info-cache
2023-07-26 front
2023-07-26 logos
2023-07-26 logo
2023-07-26 Perimeter
2023-07-26 Final
2023-07-27 make space for qr code
2023-07-27 Comment out diode
2023-07-27 bumps
2023-07-27 QR code
2023-07-28 gerber
2023-07-28 Cap fix
2023-07-28 sch. switch update
2023-07-31 Pictures
2023-08-02 Cleaned up CMOS
2023-08-02 clean
2023-08-02 3.3V
2023-08-08 Screenshots upload
2023-08-10 Schematic changes
2023-08-11 README
2023-08-11 Add files via upload
    Use Logisim program to open this file
